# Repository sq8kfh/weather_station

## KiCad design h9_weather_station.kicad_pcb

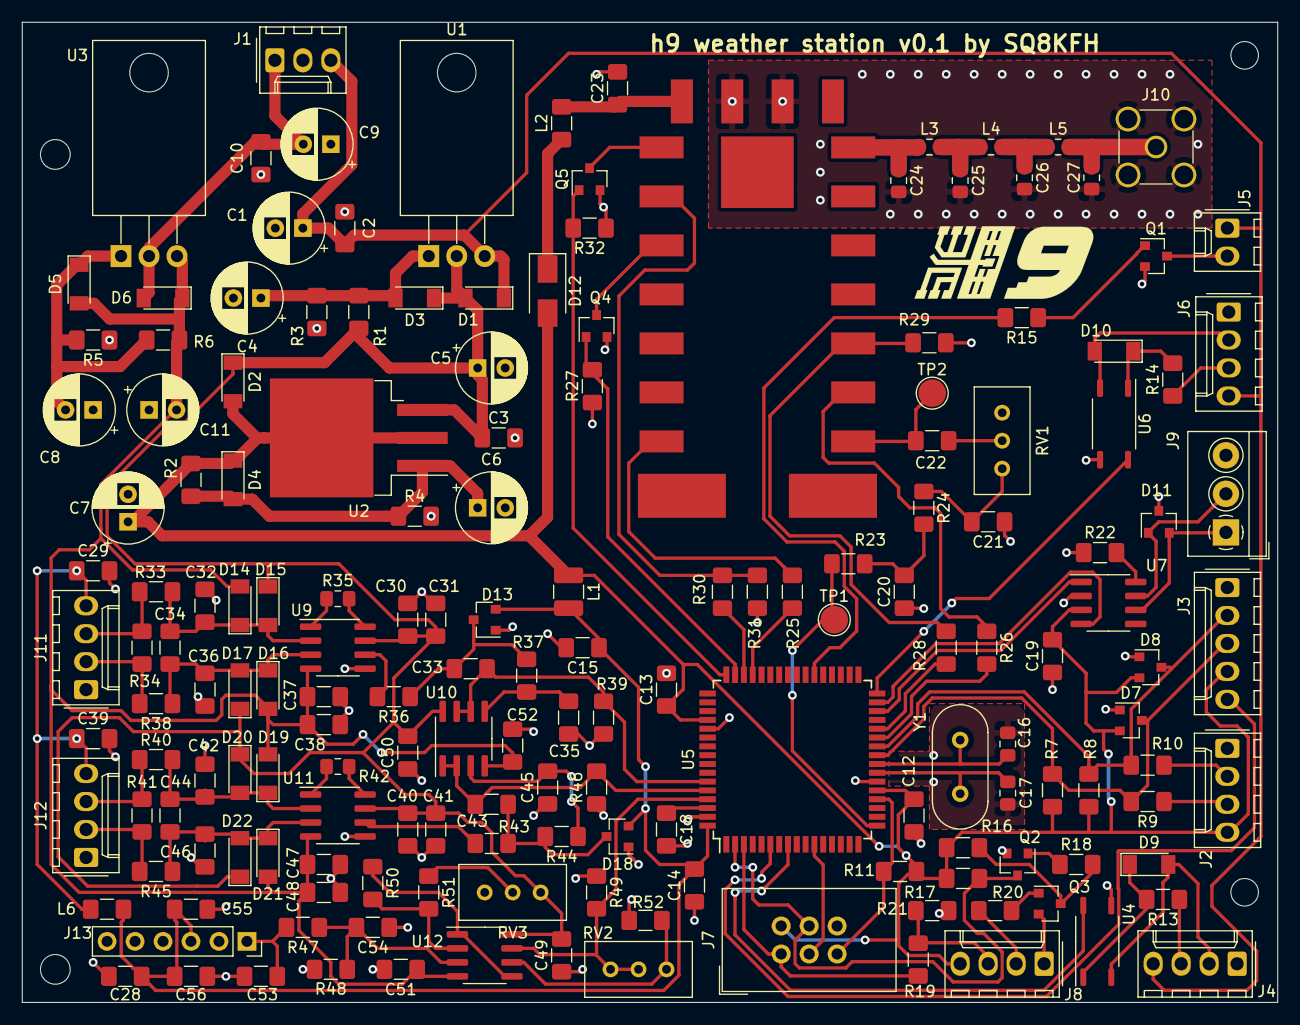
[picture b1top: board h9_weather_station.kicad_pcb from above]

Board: 2 copper layers, 114.0 x 89.0 mm, 172 parts (1 on the bottom side), 95 nets.

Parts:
C1, C4, C5, C6, C7, C8, C9, C11: 10uF; CP_Radial_D6.3mm_P2.50mm
C2, C3, C10, C12, C13, C14, C19, C23, C29, C39: 100nF; C_1206_3216Metric_Pad1.42x1.75mm_HandSolder
C15, C18, C30, C33, C35, C37, C40, C43, C45, C47, C49, C50, C51, C52: 100n; C_1206_3216Metric_Pad1.42x1.75mm_HandSolder
C16, C17: 20p; C_0805_2012Metric_Pad1.15x1.40mm_HandSolder
C20, C21: 22nF; C_1206_3216Metric_Pad1.42x1.75mm_HandSolder
C22: 2.2nF; C_1206_3216Metric_Pad1.42x1.75mm_HandSolder
C24, C27: 20pF; C_0805_2012Metric_Pad1.15x1.40mm_HandSolder
C25, C26: 36pF; C_0805_2012Metric_Pad1.15x1.40mm_HandSolder
C28, C32, C34, C36, C42, C44, C46: C_Small; C_1206_3216Metric_Pad1.42x1.75mm_HandSolder
C31, C38, C41, C48: 10u; C_1206_3216Metric_Pad1.42x1.75mm_HandSolder
C53: 470pF; C_1206_3216Metric_Pad1.42x1.75mm_HandSolder
C54, C56: 1uF; C_1206_3216Metric_Pad1.42x1.75mm_HandSolder
C55: 10nF; C_1206_3216Metric_Pad1.42x1.75mm_HandSolder
D1, D2, D3, D4, D5, D6: 1N4001; D_MiniMELF
D7, D8, D13, D18: BAT54-04; SOT-23
D9, D10: 4148; D_MiniMELF
D11: NUP2105L; SOT-23
D12: S1A; D_SMA
D14, D15, D16, D17, D19, D20, D21, D22: NC; D_MiniMELF
J1: PWR; Molex_KK-254_AE-6410-03A_1x03_P2.54mm_Vertical
J2: SHT-30; Molex_KK-254_AE-6410-04A_1x04_P2.54mm_Vertical
J3: Gravity-Lightning Sensor; Molex_KK-254_AE-6410-05A_1x05_P2.54mm_Vertical
J4: WIND SPEED; Molex_KK-254_AE-6410-04A_1x04_P2.54mm_Vertical
J5: heater switch; Molex_KK-254_AE-6410-02A_1x02_P2.54mm_Vertical
J6: T3; Molex_KK-254_AE-6410-04A_1x04_P2.54mm_Vertical
J7: AVR-ISP-6; IDC-Header_2x03_P2.54mm_Vertical
J8: UART 3.3V; Molex_KK-254_AE-6410-04A_1x04_P2.54mm_Vertical
J9: CAN; TerminalBlock_4Ucon_1x03_P3.50mm_Horizontal
J10: Conn_Coaxial; SMA_Amphenol_901-144_Vertical
J11: CMP3; Molex_KK-254_AE-6410-04A_1x04_P2.54mm_Vertical
J12: W200P; Molex_KK-254_AE-6410-04A_1x04_P2.54mm_Vertical
J13: MPX4115A; PinSocket_1x06_P2.54mm_Vertical
L1: 10u; L_1210_3225Metric_Pad1.42x2.65mm_HandSolder
L2, L6: L_Core_Ferrite_Small; L_1206_3216Metric_Pad1.42x1.75mm_HandSolder
L3, L5: 56nH; L_0805_2012Metric_Pad1.15x1.40mm_HandSolder
L4: 68nH; L_0805_2012Metric_Pad1.15x1.40mm_HandSolder
Q1, Q2, Q3: BC817; SOT-23
Q4, Q5: 2N7002; SOT-23
R1, R2: 240R; R_1206_3216Metric_Pad1.42x1.75mm_HandSolder
R3, R4, R5, R33, R38, R40, R45: R_Small; R_1206_3216Metric_Pad1.42x1.75mm_HandSolder
R6: 120R; R_1206_3216Metric_Pad1.42x1.75mm_HandSolder
R7, R8, R11, R36, R37, R43, R44: 10k; R_1206_3216Metric_Pad1.42x1.75mm_HandSolder
R9, R10: 100R; R_1206_3216Metric_Pad1.42x1.75mm_HandSolder
R12, R25, R26: 0R; R_1206_3216Metric_Pad1.42x1.75mm_HandSolder
R13, R14: 270R; R_1206_3216Metric_Pad1.42x1.75mm_HandSolder
R15, R16, R17, R18, R19, R20, R47, R48, R50, R51, R52: 1k; R_1206_3216Metric_Pad1.42x1.75mm_HandSolder
R21: 2k; R_1206_3216Metric_Pad1.42x1.75mm_HandSolder
R22: 39k; R_1206_3216Metric_Pad1.42x1.75mm_HandSolder
R23, R24: 56k; R_1206_3216Metric_Pad1.42x1.75mm_HandSolder
R27, R32: 1.8k; R_1206_3216Metric_Pad1.42x1.75mm_HandSolder
R28, R30: 1.5k; R_1206_3216Metric_Pad1.42x1.75mm_HandSolder
R29, R31: 3.3k; R_1206_3216Metric_Pad1.42x1.75mm_HandSolder
R34: NC/470k; R_1206_3216Metric_Pad1.42x1.75mm_HandSolder
R35: 1.36k; R_0805_2012Metric_Pad1.15x1.40mm_HandSolder
R39, R46, R49: NC; R_1206_3216Metric_Pad1.42x1.75mm_HandSolder
R41: 100k; R_1206_3216Metric_Pad1.42x1.75mm_HandSolder
R42: NC; R_0805_2012Metric_Pad1.15x1.40mm_HandSolder
RV1: 10k; Potentiometer_Bourns_3296W_Vertical
RV2, RV3: R_POT; Potentiometer_Bourns_3296W_Vertical
TP1: PWM_AF; TestPoint_Pad_D2.5mm
TP2: AF; TestPoint_Pad_D2.5mm
U1: LM217; TO-220-3_Horizontal_TabDown
U2: LM317; TO-263-3_TabPin2
U3: LM237; TO-220-3_Horizontal_TabDown
U4, U6: TLP185; SOIC-4_4.55x3.7mm_P2.54mm
U5: AT90CAN128-16AU; TQFP-64_14x14mm_P0.8mm
U7: MCP2551-I-SN; SOIC-8_3.9x4.9mm_P1.27mm
U8: DRA818V; DRA818
U9: AD8223; SOIC-8_3.9x4.9mm_P1.27mm
U10: NE5532; SOIC-8_3.9x4.9mm_P1.27mm
U11: AD620; SOIC-8_3.9x4.9mm_P1.27mm
U12: LM358; SOIC-8_3.9x4.9mm_P1.27mm
Y1: 12MHz; Crystal_HC49-U_Vertical

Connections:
+4V: C23.1, L2.2, U8.8
+5V: C7.1, C12.1, C13.1, C19.2, D2.2, D4.1, D7.2, D8.2, D12.2, J2.4, J3.4, J7.2, J8.4, L1.1, R2.1, R7.2, R8.2, R11.1, R16.2, R17.2, U2.2, U5.21, U5.52, U7.3
+5VA: C14.2, C15.1, C28.2, C55.2, C56.1, D13.2, D18.2, J13.3, L1.2, L6.1, U5.64
+9VA: C3.1, C5.1, C30.1, C31.2, C40.1, C41.2, C49.2, C50.2, D1.2, D2.1, D3.1, D15.1, D17.1, D20.1, D22.1, R1.1, RV3.3, U1.2, U2.3, U9.7, U10.8, U11.7, U12.8
+12V: C1.1, C2.1, D1.1, J1.3, J4.4, J5.1, J6.4, U1.3
-9VA: C11.2, C37.1, C38.2, C47.1, C48.2, C51.1, C52.1, D5.2, D6.1, D14.2, D16.2, D19.2, D21.2, R6.2, U3.3, U9.4, U10.4, U11.4, U12.4
/MCU/CANRX: U5.31, U7.4
/MCU/CANTX: U5.30, U7.1
/MCU/LS_INT: J3.5, U5.6
/MCU/RX0: J7.4, Q2.3, R17.1, U5.2
/MCU/SCL: D7.3, J3.3, R7.1, R9.2, U5.25
/MCU/SDA: D8.3, J3.2, R8.1, R10.2, U5.26
/MCU/T0: U5.32, U6.6
/MCU/T3: U4.6, U5.8
/MCU/TX0: J7.1, R19.1, U5.3
ADC_CMP3: C33.1, R39.2, U5.59, U10.6, U10.7
ADC_MPX4115A: R49.2, RV2.2, RV2.3, U5.61, U12.7
ADC_W200P: C43.1, R46.2, U5.60, U10.1, U10.2
AF_OUT: R23.2, TP1.1, U5.17
DRA_HL: Q5.1, R32.2, U5.48
DRA_PD: R30.1, U5.46
DRA_PTT: Q4.1, R27.2, U5.47
DRA_SQL: R25.1, U5.45
GND: C1.2, C2.2, C3.2, C4.2, C5.2, C6.2, C7.2, C8.1, C9.1, C10.1, C11.1, C12.2, C13.2, C16.2, C17.2, C19.1, C20.1, C21.1, C23.2, C24.2, C25.2, C26.2, C27.2, D7.1, D8.1, D11.3, J1.2, J2.1, J3.1, J4.1, J6.1, J7.6, J8.1, J9.3, J10.2, Q1.2, Q2.2, Q3.2, Q4.2, Q5.2, R3.2, R4.2, R5.1, R12.1, R21.1, R22.1, R27.1, R29.1, R31.1, R32.1, RV1.3, U4.4, U5.22, U5.53, U6.4, U7.2, U8.9, U8.10
GNDA: C14.1, C15.2, C18.2, C28.1, C29.2, C30.2, C31.1, C32.2, C35.1, C36.1, C37.2, C38.1, C39.2, C40.2, C41.1, C42.2, C45.1, C46.1, C47.2, C48.1, C49.1, C50.1, C51.2, C52.2, C53.1, C54.1, C55.1, C56.2, D13.1, D18.1, J11.1, J12.1, J13.2, R12.2, R39.1, R46.1, R48.1, R49.1, R52.2, RV3.1, U5.63, U9.5, U11.5
unnamed: C4.1, D3.2, R1.2, R3.1, U1.1
unnamed: C6.1, D4.2, R2.2, R4.1, U2.1
unnamed: C8.2, D5.1, R5.2, R6.1, U3.1
unnamed: C9.2, C10.2, D6.2, J1.1, U3.2
unnamed: C16.1, U5.24, Y1.1
unnamed: C17.1, U5.23, Y1.2
unnamed: C18.1, U5.62
unnamed: C20.2, R23.1, R24.2
unnamed: C21.2, R24.1, RV1.1
unnamed: C22.1, TP2.1, U8.18
unnamed: C22.2, RV1.2
unnamed: C24.1, L3.1, U8.12
unnamed: C25.1, L3.2, L4.1
unnamed: C26.1, L4.2, L5.1
unnamed: C27.1, J10.1, L5.2
unnamed: C29.1, C39.1, J11.4, J12.4, L6.2
unnamed: C32.1, C34.2, D14.1, D15.2, R33.1, U9.2
unnamed: C33.2, D13.3, R36.1, R37.2
unnamed: C34.1, C36.2, D16.1, D17.2, R38.1, U9.3
unnamed: C35.2, R37.1, U10.5
unnamed: C42.1, C44.2, D19.1, D20.2, R40.1, U11.2
unnamed: C43.2, D18.3, R43.1, R44.2
unnamed: C44.1, C46.2, D21.1, D22.2, R45.1, U11.3
unnamed: C45.2, R44.1, U10.3
unnamed: C53.2, J13.1, R47.2
unnamed: C54.2, R47.1, R48.2, U12.3
unnamed: D9.1, R13.2, U4.1
unnamed: D9.2, J4.2, U4.3
unnamed: D10.1, R14.2, U6.1
unnamed: D10.2, J6.2, U6.3
unnamed: D11.1, J9.2, U7.7
unnamed: D11.2, J9.1, U7.6
unnamed: D12.1, L2.1
unnamed: J2.2, R10.1
unnamed: J2.3, R9.1
unnamed: J4.3, R13.1
unnamed: J5.2, Q1.3
unnamed: J6.3, R14.1
unnamed: J7.3, U5.11
unnamed: J7.5, R11.2, U5.20
unnamed: J8.2, R20.2
unnamed: J8.3, R19.2, R21.2
unnamed: J11.2, R34.1, R38.2
unnamed: J11.3, R33.2, R34.2
unnamed: J12.2, R41.1, R45.2
unnamed: J12.3, R40.2, R41.2
unnamed: Q1.1, R15.1
unnamed: Q2.1, R18.1
unnamed: Q3.1, R20.1
unnamed: Q3.3, R16.1, R18.2
unnamed: Q4.3, U8.5
unnamed: Q5.3, U8.7
unnamed: R15.2, U5.38
unnamed: R22.2, U7.8
unnamed: R25.2, U8.1
unnamed: R26.1, U8.17
unnamed: R28.1, R29.2, U8.16
unnamed: R30.2, R31.2, U8.6
unnamed: R35.1, U9.1
unnamed: R35.2, U9.8
unnamed: R36.2, U9.6
unnamed: R42.1, U11.1
unnamed: R42.2, U11.8
unnamed: R43.2, U11.6
unnamed: R50.1, U12.1, U12.5
unnamed: R50.2, R51.2, U12.2
unnamed: R51.1, RV3.2
unnamed: R52.1, RV2.1, U12.6
RX1: R26.2, U5.27
TX1: R28.2, U5.28

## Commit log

2020-12-24 Init v0.1
